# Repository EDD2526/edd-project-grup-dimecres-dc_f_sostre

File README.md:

# Projecte Eines Sostre Solar 

>**Autors: Nabel Khrourouch i Marc Baillo** 
>**Versió: 0.2 **

----------

## Objectiu

Dissenyar i implementar en una PCB, un sistema electronic del vehicle com es un sostre solar. S’implementara una etapa de regulacio, microcontrolador,  bus CAN, I2C / SPI, USART i botons. 
I que incloguiu les següents caracteristiques:
- Motor del vidre amb el seu final de carrera. 
- Motor de la cortineta.
- Llums ambientals (LED RGB amb bus digital)
- Mecanisme antiatrapament (sensor digital de corrent).

## Diagrama de blocs

### Descripció/funcionalitat de cada bloc

  * Power: En aquest bloc posem la partt relacionada con 2 etapes, la de la alimentació i la de potencia. (LDO y Buck converter i el H-Bridge)
  * Microcontrolador: en aquest bloc posem les parts que tenen molt que veure amb el microcontrolador com cristal oscilador, ICSP, botonera, filtre pi, reset manual, LEDs de prova.
  * Analógica: part del sistema que és analogic i per tant la agrupem, aquí veiem el sensor de anti-atrapament.
  * Digital: part on están els components més purament digitals, como el USART, el transceiver CAN, el Sensor de Final de Carrera o LED RGB. 

-----------

## Requisits / Especificacions

  * Alimentació; 12V, regulada a 3V3
  * Microcontrolador PIC24hj128gp502
  * Motor del vidre amb el seu final de carrera. 
  * Motor de la cortineta.
  * Llums ambientals (LED RGB amb bus digital)
  * Mecanisme antiatrapament (sensor digital de corrent).

-----------

## Components

| Descripció                        | Ref                        | Package                  | Datasheet | Proveïdor | Preu (per u) | Unitats |
|----------------------------------|----------------------------|--------------------------|-----------|-----------|--------------|---------|
| Microcontrolador                | PIC24HJ128GP502           | TQFP-44                  | [Datasheet](https://ww1.microchip.com/downloads/aemDocuments/documents/OTH/ProductDocuments/DataSheets/70293G.pdf) | [Mouser](https://www.mouser.es/ProductDetail/Microchip-Technology/PIC24HJ128GP504-E-PT?qs=Fllw7YelV3%252B64KTDe2rRTg%3D%3D) | 6,85€ | 1x |
| Regulador de Tensió             | LM1117                    | SOT-223 / TO-252-3       | [Datasheet](https://www.ti.com/lit/ds/symlink/lm1117.pdf) | [Mouser](https://www.mouser.es/ProductDetail/Texas-Instruments/LM1117IMPX-3.3-NOPB?qs=X1J7HmVL2ZG7K12CpArCeA%3D%3D) | 0,89€ | 1x |
| Buck Converter (DC/DC)          | LM2596                    | TO-220-5                 | [Datasheet](https://www.onsemi.com/pdf/datasheet/lm2596-d.pdf) | [Mouser](https://www.mouser.es/ProductDetail/onsemi/LM2596DSADJG?qs=atIEnC%2F2K4W1Dy%252BFjrRjIQ%3D%3D) | 2€ | 1x |
| H-Bridge (Doble)                | L298N                     | Multiwatt-15             | [Datasheet](https://www.st.com/resource/en/datasheet/l298.pdf) | [Mouser](https://www.mouser.es/ProductDetail/STMicroelectronics/L298N?qs=gr8Zi5OG3Mj6jDtNclcF9Q%3D%3D&srsltid=AfmBOoqfHqg2YnbNWZkkZ0kC8gS-It04lRCKKxTP2hRawLswU3FHokk-) | 9,94€ | 1x |
| Transceiver CAN                 | SN65HVD232DR                 | SOIC-8                   | [Datasheet](https://www.ti.com/lit/ds/symlink/sn65hvd230.pdf?ts=1777297017115&ref_url=https%253A%252F%252Fwww.ti.com%252Fproduct%252FSN65HVD230) | [Mouser](https://eu.mouser.com/ProductDetail/Texas-Instruments/SN65HVD232DR?qs=QViXGNcIEAtY%252BrViRMr46w%3D%3D) | 1,87€  | 1x |
| Driver USART                    | MAX3232                   | SSOP-16                  | [Datasheet](https://www.mouser.es/datasheet/3/1014/1/MAX3222-MAX3241.pdf) | [Mouser](https://www.mouser.es/ProductDetail/Analog-Devices-Maxim-Integrated/MAX3232CUE%2bT?qs=CDqwynd4ZNq6sBxRCl3%2FVw%3D%3D) | 6,99€ | 1x |
| Conector                        | DE9                       | DSUB-9_Socket            | [Datasheet](https://www.te.com/commerce/DocumentDelivery/DDEController?Action=srchrtrv&DocNm=2301843&DocType=Customer+Drawing&DocLang=English&PartCntxt=2301843-1&DocFormat=pdf) | [Mouser](https://www.mouser.es/ProductDetail/TE-Connectivity-AMP/2301843-1?qs=rrS6PyfT74crws9wAQVNoA%3D%3D&mgh=1&vip=1&utm_id=19103542967&utm_source=google&utm_medium=cpc&utm_marketing_tactic=emeacorp&gad_source=1&gad_campaignid=19103548274&gbraid=0AAAAADn_wf2KTMAEN9aavrmuZXjiN2vqm&gclid=Cj0KCQjw7IjOBhDyARIsAFzrWQzWx8kAOC9-xeCib2TtXzouOFVkeyjK2X-mWbgX7vQpQhIDmcFKVOEaAr35EALw_wcB) | 1,9€ | 2x |
| Conector (Batería i Motors)                       | 282837-2                       | THT          | [Datasheet](https://www.te.com/commerce/DocumentDelivery/DDEController?Action=srchrtrv&DocNm=1-1773458-1_EURO_STYLE_QRG&DocType=Data%20Sheet&DocLang=English&PartCntxt=3-282837-2&DocFormat=pdf) | [Mouser](https://www.mouser.es/ProductDetail/TE-Connectivity/3-282837-2?qs=gdajpSf3VLdF%252BeXqJMAnlA%3D%3D&utm_id=20109199436&utm_source=google&utm_medium=cpc&utm_marketing_tactic=emeacorp&gad_source=1&gad_campaignid=20109199436&gbraid=0AAAAADn_wf3bSykfoqBB3E0CfDtWEe629&gclid=Cj0KCQjw7IjOBhDyARIsAFzrWQyU83zMWuFV4gqDL4u1LgEcrHvitAufowkzTkPBhEg_k3zvYB4tBVIaAj3AEALw_wcB) | 9,38€ | 3x |
| Sensor (corrent) Anti-Atrapament              | INA219                    | SOIC-8                      | [Datasheet](https://www.ti.com/lit/ds/symlink/ina219.pdf) | [Mouser](https://www.mouser.es/ProductDetail/) | 4,23€ | 2x |
| Sensor Final de Carrera         | A1101                     | SOT-23                   | [Datasheet](https://www.allegromicro.com/~/media/files/datasheets/a110x-datasheet.pdf) | [Mouser](https://www.mouser.es/ProductDetail/Allegro-MicroSystems/A1101EUA-T?qs=pUKx8fyJudAoca%252BrN0Sfug%3D%3D&srsltid=AfmBOopmzx3dJfmaMgARzIOmuFdzof038kPjXIFZjNx3_Dk0axwEeuXz) | 1,18€ | 2x |
| Opamp Doble Comparador        | LM393                     | SOIC-8                  | [Datasheet](https://www.ti.com/lit/ds/symlink/lm2903b.pdf?ts=1774335179874&ref_url=https%253A%252F%252Fwww.mouser.pl%252F) | [Mouser](https://www.mouser.es/ProductDetail/Texas-Instruments/LM393AP?qs=LfG3tU9ud8C8WR6rae7e8w%3D%3D&utm_id=20109199436&utm_source=google&utm_medium=cpc&utm_marketing_tactic=emeacorp&gad_source=1&gad_campaignid=20109199436&gbraid=0AAAAADn_wf3bSykfoqBB3E0CfDtWEe629&gclid=Cj0KCQjw7IjOBhDyARIsAFzrWQwk6DXPkYJ3-Ag5UdBtY40izdCAfFJImBQIx_JyaWhi5W70RpnD0e8aAgx9EALw_wcB) | 0,31 | 1x |
| Cristal Oscilador               | ECS-80-20-20BM-EN-TR      | 7mm x 5mm                | [Datasheet](https://www.mouser.es/datasheet/3/294/1/csm_8mr.pdf) | [Mouser](https://www.mouser.es/ProductDetail/ECS/ECS-80-20-20BM-EN-TR?qs=3Rah4i%252BhyCEvSjMjFbrNOA%3D%3D&utm_id=9882080341&utm_source=google&utm_medium=cpc&utm_marketing_tactic=emeacorp&gad_source=1&gad_campaignid=9882080341&gbraid=0AAAAADn_wf2VPwruzVVuU5TdtfDNM-71c&gclid=CjwKCAjwpcTNBhA5EiwAdO1S9kbEmbKF8UUMwaVP0zWJXkCwjEh6ns86OOaH_PQxj7KPIVRFoQ-tjhoCMYIQAvD_BwE) | 0,86€ | 1x |
| Ferrita                         | BLM21                     | 0805                     | [Datasheet](https://www.mouser.es/datasheet/3/76/1/ENFA0005.pdf) | [Mouser](https://www.mouser.es/ProductDetail/Murata-Electronics/BLM21PG600SN1D?qs=LbqjZSvnDswFXSg06XQ50A%3D%3D&utm_id=9882080341&utm_source=google&utm_medium=cpc&utm_marketing_tactic=emeacorp&gad_source=1&gad_campaignid=9882080341&gbraid=0AAAAADn_wf2r1gIBG4HB31JwCLchDktw_&gclid=Cj0KCQjw9-PNBhDfARIsABHN6-1kCnzr_LU1mZd8ISSiD6a4Y2yPfWM2slAP8zejLYN4QiWVlEgd_j4aAjKhEALw_wcB) | 0,10€ | 1x |
| Switch (Pulsador) Reset y Botonera                 | B3F-1002                  | THT                      | [Datasheet](https://www.mouser.es/datasheet/3/39/1/en_b3f.pdf) | [Mouser](https://www.mouser.es/ProductDetail/Omron-Electronics/B3F-1002?qs=lK7M36XCk6Jk6Tf1a0ilbA%3D%3D&mgh=1&vip=1&utm_source=chatgpt.com) | 0,27€ | 6x |
| LED blau                        | LTST-C170TBKT             | LED_SMD                     | [Datasheet](https://www.mouser.com/catalog/specsheets/Lite-On-LTST-C170TBKT.pdf) | [Mouser](https://www.mouser.es/ProductDetail/LITEON/LTST-C170TBKT?qs=0uL0gcxEMop2ooGmIUzw3A%3D%3D&mgh=1&vip=1&utm_source=chatgpt.com) | 0,23€ | 1x |
| LED vermell                     | LTST-C170KRKT             | LED_SMD                     | [Datasheet](https://www.mouser.com/catalog/specsheets/Lite-On-LTST-C170KRKT.pdf) | [Mouser](https://www.mouser.es/ProductDetail/LITEON/LTST-C170KRKT?qs=NUb82WqeCyrVOID%2Fxt4rgA%3D%3D&utm_id=9882080341&utm_source=google&utm_medium=cpc&utm_marketing_tactic=emeacorp&gad_source=1&gad_campaignid=9882080341&gbraid=0AAAAADn_wf35b0MW3nfCvSzMlg6XwcaGU&gclid=CjwKCAjwyYPOBhBxEiwAgpT8P6xYGFYLA1kJHVwio65sFBFYBpuG5qPQD4Bkm8pgxI7bRmXtEGCxWBoC7pMQAvD_BwE) | 0,14€ | 1x |
| LED RGB                         | WS2812                    | LED_SMD                 | [Datasheet](https://www.tme.eu/Document/01c0100fee68667af99767edc3a7fee2/WS2812B-MINI.pdf) | [TME](https://www.tme.eu/es/details/ws2812b-mini/leds-smd-de-colores/worldsemi/?utm_source=google&utm_medium=cpc&utm_campaign=HISZPANIA%20%5BDSA%5D&utm_content=&campaign_id=18880888776&gad_source=1&gad_campaignid=18880888776&gbraid=0AAAAADyylhLJURluAY7jUeNc8-F-2bfAx&gclid=Cj0KCQjw7IjOBhDyARIsAFzrWQzO_PW3O0VVMhyARWr_1LRVY-vRQsT44Hck0vcMLTjOFT9BO_EXdCEaAkMFEALw_wcB) | 0,42€ | 1x |
| Level shifter (buffer)                        | 74AHCT1G125            | SOT-553              | [Datasheet](https://www.ti.com/lit/ds/symlink/sn74ahct1g125.pdf?ts=1774340206599&ref_url=https%253A%252F%252Fwww.mouser.dk%252F) | [Mouser](https://www.mouser.es/ProductDetail/Texas-Instruments/74AHCT1G125DBVTG4?qs=AsTZqt%2FmeqnddshDG5FV%2Fw%3D%3D&utm_id=20109199436&utm_source=google&utm_medium=cpc&utm_marketing_tactic=emeacorp&gad_source=1&gad_campaignid=20109199436&gbraid=0AAAAADn_wf3bSykfoqBB3E0CfDtWEe629&gclid=Cj0KCQjw7IjOBhDyARIsAFzrWQxSsxXdPjF95Q5vX5TJ7WjE_NFE_Jxv0JufhHPBQC8U8gs4R3YIGEkaAvcBEALw_wcB) | 0,93€ | 1x |

-----------

## Historial de canvis

| Data     | Autor           | Branch | Versió   | Descripció                                                                 |
|----------|-----------------|--------|----------|----------------------------------------------------------------------------|
| 10/03/26 | Nabel i Marc    | Master | versió 1 | Seleccionem els components i creem la primera versió del Diagrama de Bloc |
| 14/03/26 | Nabel           | Master | versió 2 | Actualització del Diagrama de Bloc                                        |
| 16/03/26 | Marc            | Master | versió 1 | Esquemàtic: creació dels subapartats del projecte                         |
| 17/03/26 | Marc            | Master | versió 2 | Esquemàtic: faig la part del uC i de Digital                              |
| 17/03/26 | Nabel           | Master | versió 3 | Esquemàtic: faig la part de power i analògica                             |
| 22/03/26 | Marc            | Master | versió 4 | Esquemàtic: correcció d’errades i assignació de footprints                |
| 24/03/26 | Nabel           | Master | versió 1 | Layout: faig el rutejat de la majoria dels components                     |
| 24/03/26 | Marc            | Master | versió 2 | Layout: corregeixo algunes coses                                          |
| 30/03/26 | Nabel           | Master | versió 3 | Layout: rutejat part Digital                                              |
| 31/03/26 | Marc            | Master | versió 4 | Layout: treballo part potencia, H_Bridge                                  |
| 08/04/26 | Marc i Nabel    | Master | versió 5 | Layout: treballem a classe i l'intentem posar a punt                      |
| 15/04/26 | Marc i Nabel    | Master | versió 6 | Layout: corregim algunes coses com tema de plans i posar plans de massa digital i power |
| 27/04/26 | Nabel           | Master | versió 1 | Faig el pressupost                                                       |
| 28/04/26 | Marc            | Master | versió 7 | Layout: acabo el Layout posant uns canvis proposats pel professor         |

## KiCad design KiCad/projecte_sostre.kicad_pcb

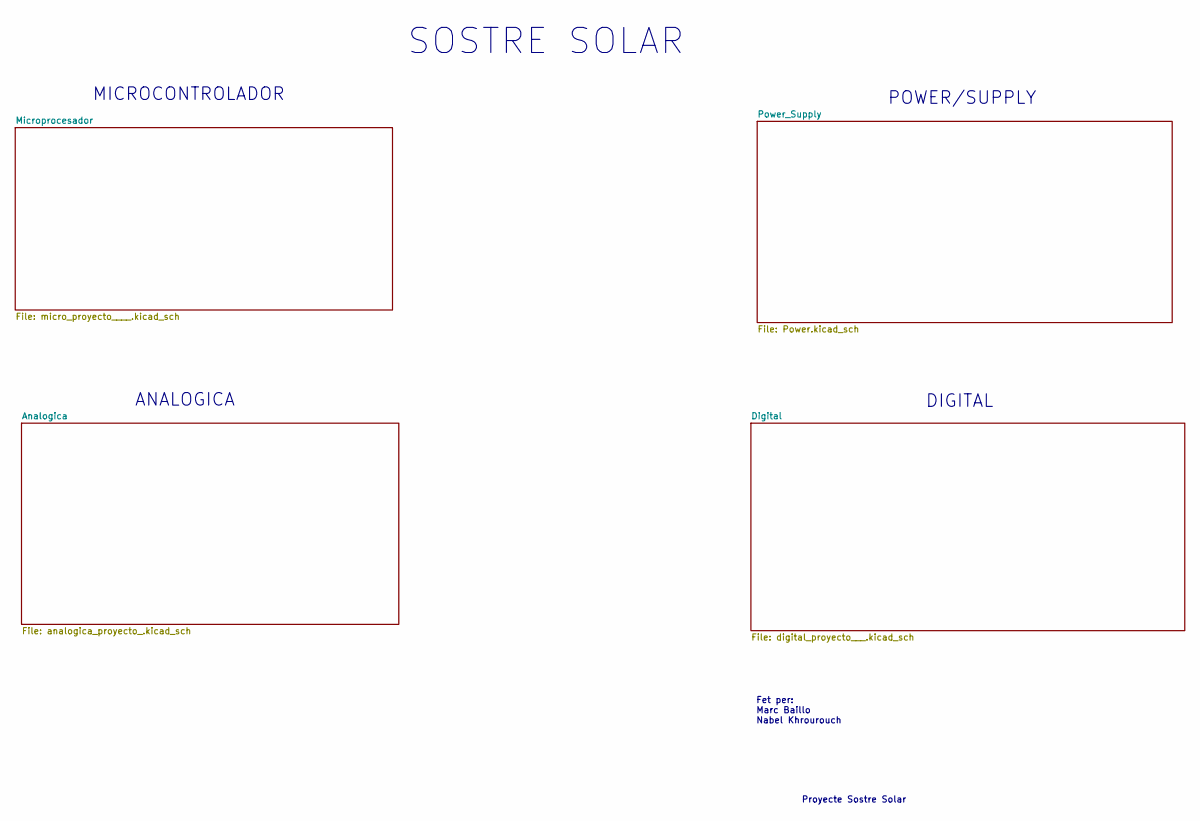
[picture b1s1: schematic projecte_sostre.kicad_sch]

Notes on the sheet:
SOSTRE SOLAR
Proyecte Sostre Solar
MICROCONTROLADOR
POWER/SUPPLY
ANALOGICA
Fet per: Marc Baillo Nabel Khrourouch
DIGITAL

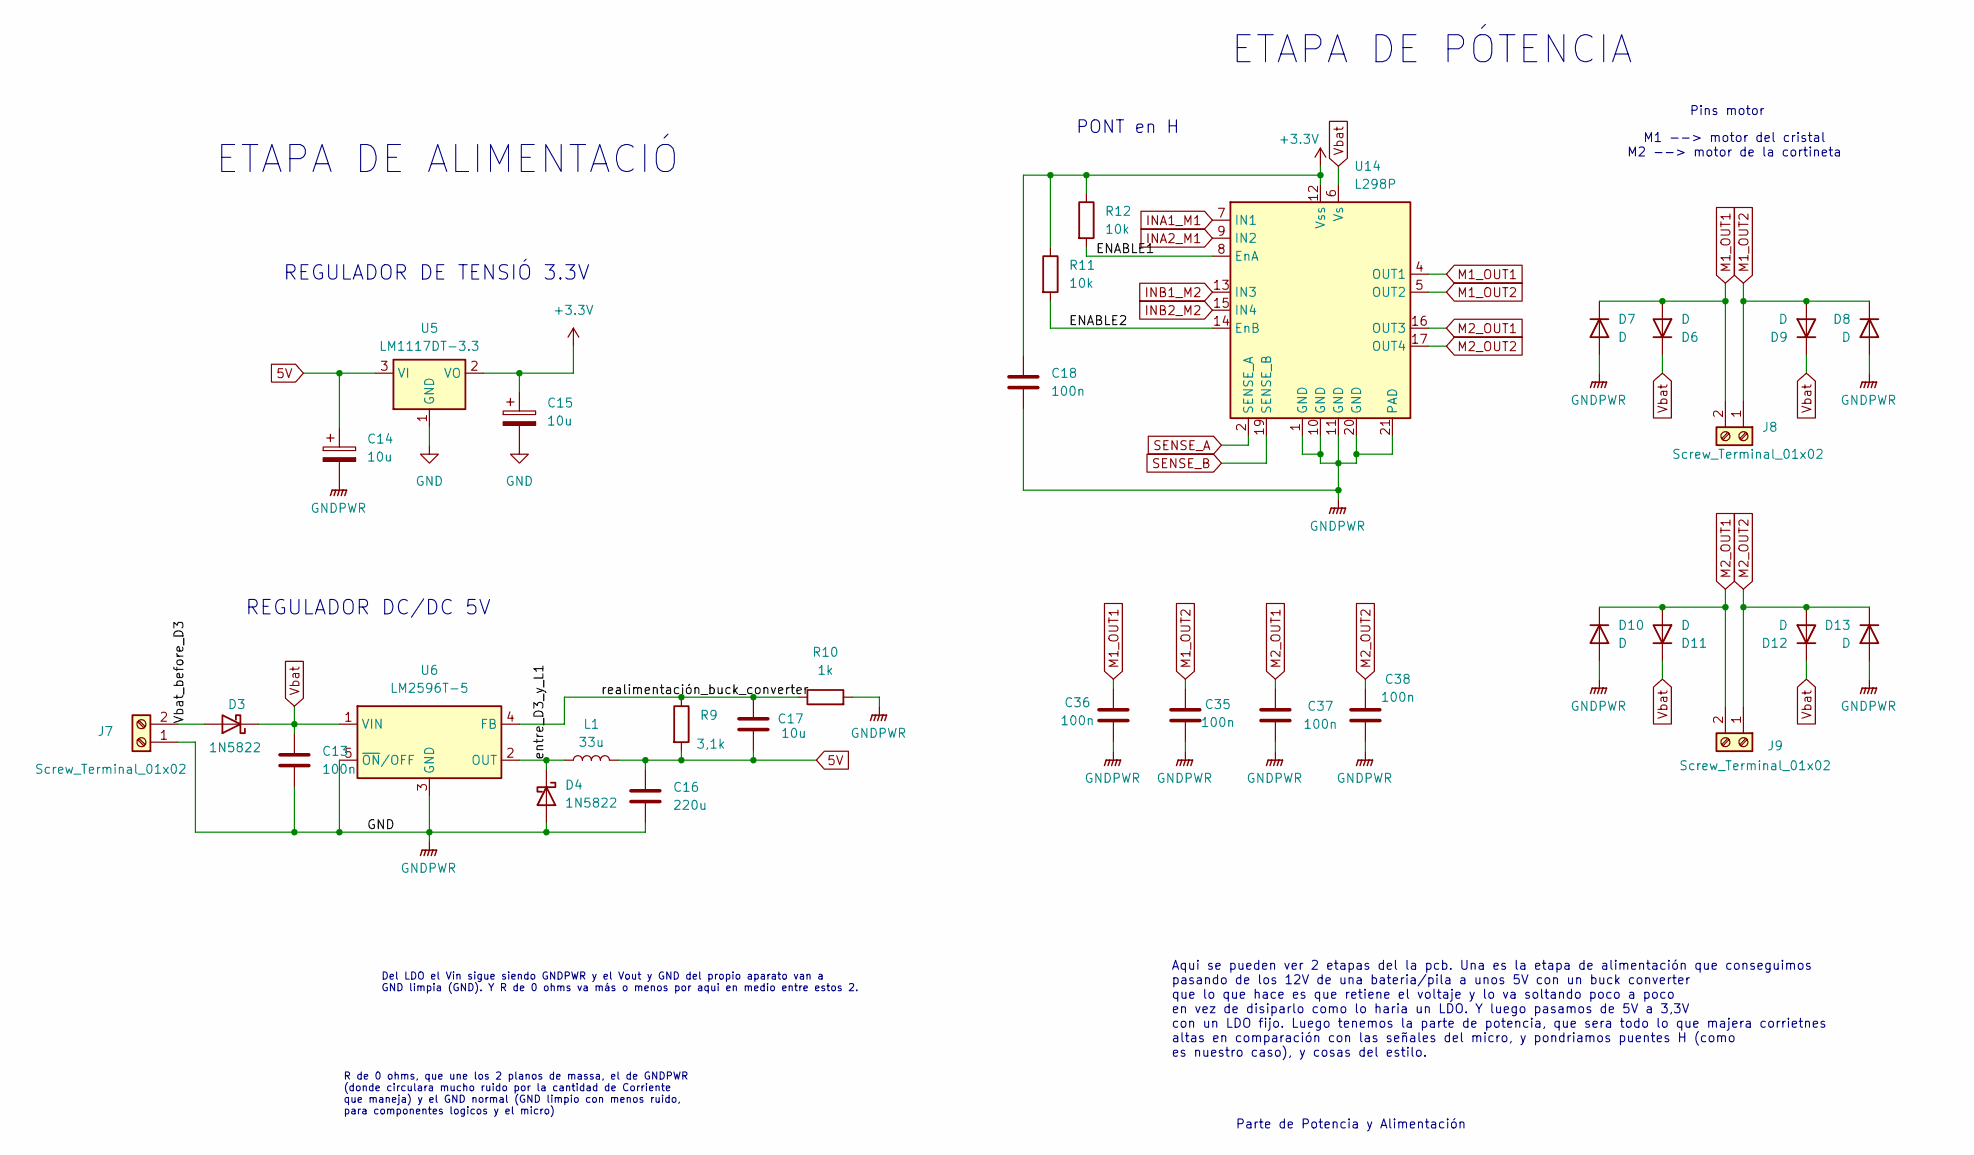
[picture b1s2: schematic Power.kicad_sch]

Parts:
C13, C18, C35, C36, C37, C38: 100n; C_0805_2012Metric
C14, C15, C17: 10u; C_0805_2012Metric
C16: 220u; C_0805_2012Metric
D3, D4: 1N5822; D_DO-201AD_P15.24mm_Horizontal
D6, D7, D8, D9, D10, D11, D12, D13: D; D_SMA
J7, J8, J9: Screw_Terminal_01x02; TerminalBlock_MaiXu_MX126-5.0-02P_1x02_P5.00mm
L1: 33u; L_1210_3225Metric
R9: 3,1k; R_0805_2012Metric
R10: 1k; R_0805_2012Metric
R11, R12: 10k; R_0805_2012Metric
U5: LM1117DT-3.3; TO-252-3_TabPin2
U6: LM2596T-5; TO-220-5_P3.4x3.7mm_StaggerOdd_Lead3.8mm_Vertical
U14: L298P; Infineon_SOIC-20W_7.6x12.8mm_P1.27mm

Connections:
5V: C14.1, C16.1, C17.2, L1.2, R9.2, U5.3 (VI); also elsewhere on the board
+3.3V: C15.1, C18.1, R11.1, R12.1, U5.2 (VO), U14.12 (Vss); also elsewhere on the board
/Power_Supply/ENABLE1: R12.2, U14.8 (EnA)
/Power_Supply/ENABLE2: R11.2, U14.14 (EnB)
/Power_Supply/Vbat_before_D3: D3.2 (A), J7.2
/Power_Supply/entre_D3_y_L1: D4.1 (K), L1.1, U6.2 (OUT)
/Power_Supply/realimentación_buck_converter: C17.1, R9.1, R10.1, U6.4 (FB)
GND: C13.2, C14.2, C15.2, C16.2, C18.2, C35.2, C36.2, C37.2, C38.2, D4.2 (A), D7.2 (A), D8.2 (A), D10.2 (A), D13.2 (A), J7.1, R10.2, U5.1 (GND), U6.3 (GND), U6.5 (~ON/OFF), U14.1 (GND), U14.10 (GND), U14.11 (GND), U14.20 (GND), U14.21 (PAD); also elsewhere on the board
INA1_M1: U14.7 (IN1); also elsewhere on the board
INA2_M1: U14.9 (IN2); also elsewhere on the board
INB1_M2: U14.13 (IN3); also elsewhere on the board
INB2_M2: U14.15 (IN4); also elsewhere on the board
M1_OUT1: C36.1, D6.2 (A), D7.1 (K), J8.2, U14.4 (OUT1)
M1_OUT2: C35.1, D8.1 (K), D9.2 (A), J8.1, U14.5 (OUT2)
M2_OUT1: C37.1, D10.1 (K), D11.2 (A), J9.2, U14.16 (OUT3)
M2_OUT2: C38.1, D12.2 (A), D13.1 (K), J9.1, U14.17 (OUT4)
SENSE_A: U14.2 (SENSE_A); also elsewhere on the board
SENSE_B: U14.19 (SENSE_B); also elsewhere on the board
Vbat: C13.1, D3.1 (K), D6.1 (K), D9.1 (K), D11.1 (K), D12.1 (K), U6.1 (VIN), U14.6 (Vs); also elsewhere on the board

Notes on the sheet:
Parte de Potencia y Alimentación
PONT en H
R de 0 ohms, que une los 2 planos de massa, el de GNDPWR (donde circulara mucho ruido por la cantidad de Corriente que maneja) y el GND normal (GND limpio con menos ruido, para componentes logicos y el micro)
Aqui se pueden ver 2 etapas del la pcb. Una es la etapa de alimentación que conseguimos pasando de los 12V de una bateria/pila a unos 5V con un buck converter que lo que hace es que retiene el voltaje y lo va soltando poco a poco en vez de disiparlo como lo haria un LDO. Y luego pasamos de 5V a 3,3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
M1 --> motor del cristal M2 --> motor de la cortineta
REGULADOR DC/DC 5V
ETAPA DE PÓTENCIA
ETAPA DE ALIMENTACIÓ
REGULADOR DE TENSIÓ 3.3V
Del LDO el Vin sigue siendo GNDPWR y el Vout y GND del propio aparato van a GND limpia (GND). Y R de 0 ohms va más o menos por aqui en medio entre estos 2.
Pins motor

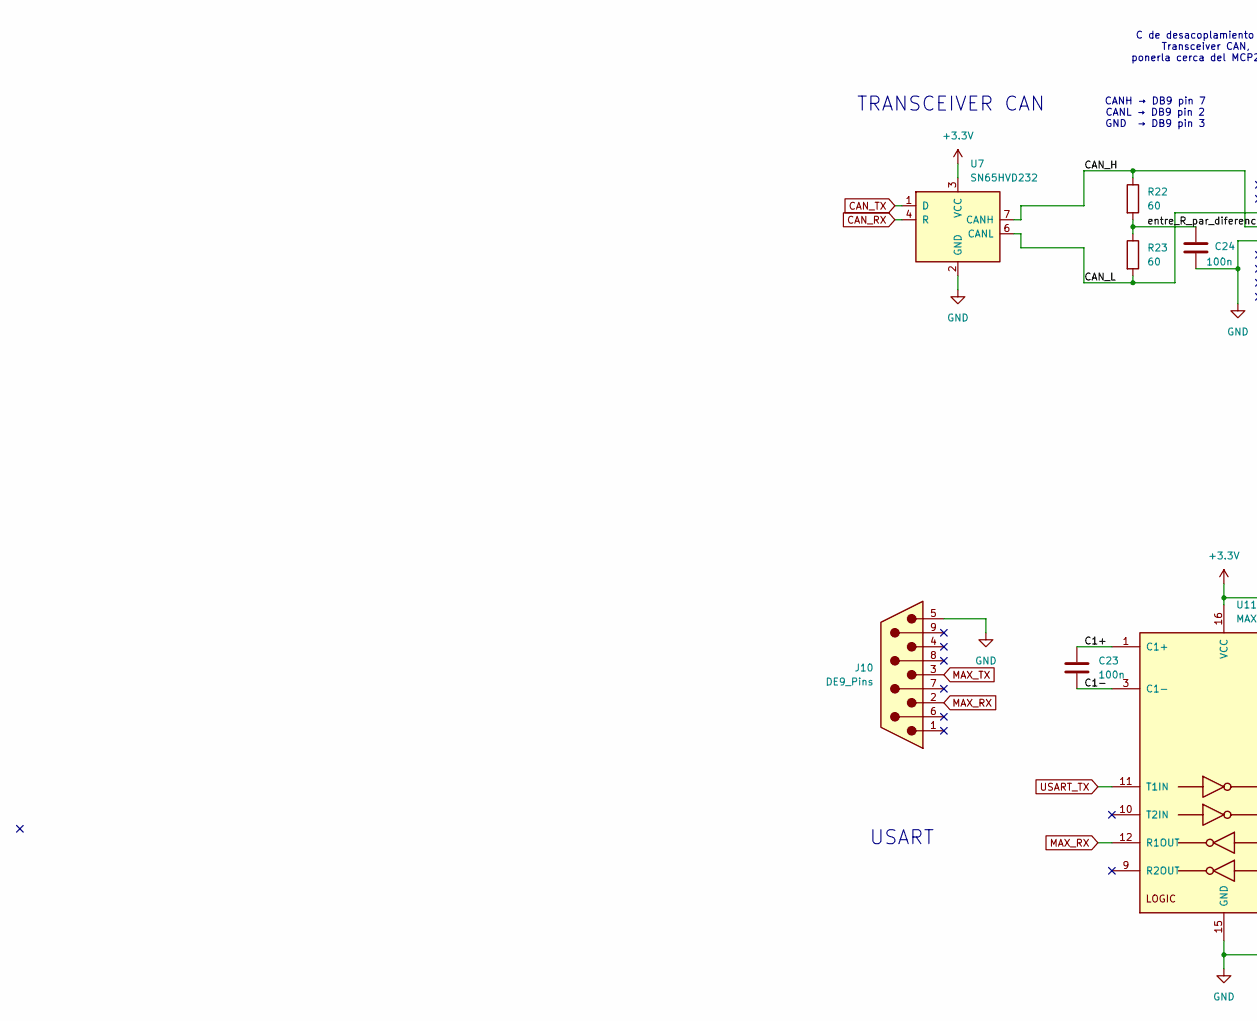
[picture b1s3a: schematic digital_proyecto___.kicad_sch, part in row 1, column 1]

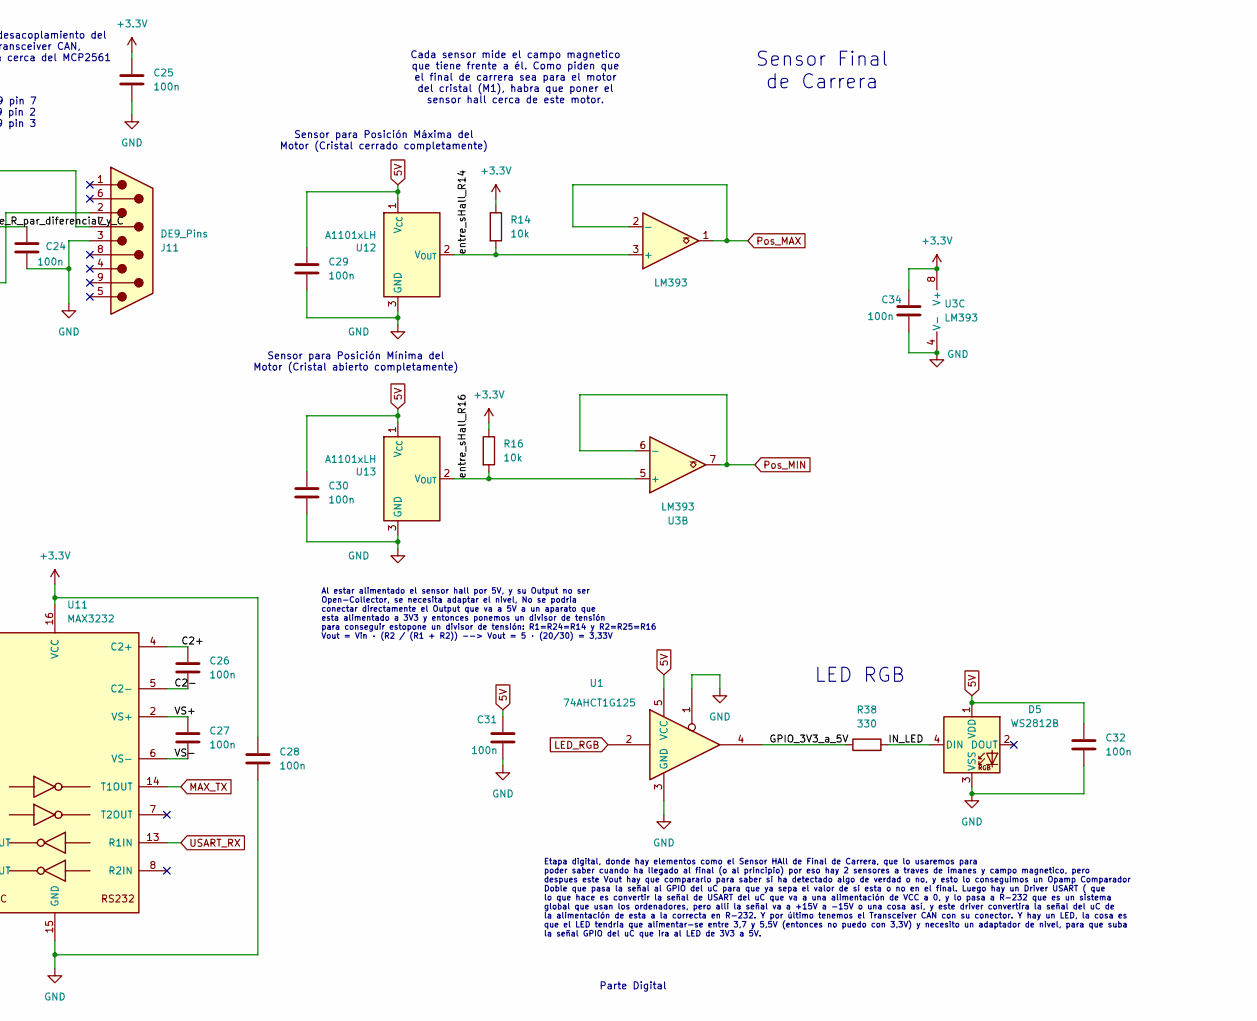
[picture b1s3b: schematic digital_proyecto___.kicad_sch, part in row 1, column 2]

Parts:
C23, C24, C25, C26, C27, C28, C29, C30, C31, C32, C34: 100n; C_0805_2012Metric
D5: WS2812B; LED_WS2812B_PLCC4_5.0x5.0mm_P3.2mm
J10, J11: DE9_Pins; DSUB-9_Pins_Horizontal_P2.77x2.54mm_EdgePinOffset9.40mm
R14, R16: 10k; R_0805_2012Metric
R22, R23: 60; R_0805_2012Metric
R38: 330; R_0805_2012Metric
U1: 74AHCT1G125; SOT-23-5_HandSoldering
U3: LM393; SOIC-8_3.9x4.9mm_P1.27mm
U7: SN65HVD232; SOIC-8_3.9x4.9mm_P1.27mm
U11: MAX3232; SOIC-16_3.9x9.9mm_P1.27mm
U12, U13: A1101xLH; SOT-23W

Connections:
5V: C29.1, C30.1, C31.1, C32.1, D5.1 (VDD), U1.5 (VCC), U12.1 (V_{CC}), U13.1 (V_{CC}); also elsewhere on the board
+3.3V: C25.1, C28.1, C34.1, R14.1, R16.1, U3.8 (V+), U7.3 (VCC), U11.16 (VCC); also elsewhere on the board
/Digital/C1+: C23.1, U11.1 (C1+)
/Digital/C1-: C23.2, U11.3 (C1-)
/Digital/C2+: C26.1, U11.4 (C2+)
/Digital/C2-: C26.2, U11.5 (C2-)
/Digital/CAN_H: J11.7, R22.1, U7.7 (CANH)
/Digital/CAN_L: J11.2, R23.2, U7.6 (CANL)
/Digital/GPIO_3V3_a_5V: R38.1, U1.4
/Digital/IN_LED: D5.4 (DIN), R38.2
/Digital/VS+: C27.1, U11.2 (VS+)
/Digital/VS-: C27.2, U11.6 (VS-)
/Digital/entre_R_par_diferencial_y_C: C24.1, R22.2, R23.1
/Digital/entre_sHall_R14: R14.2, U3.3 (+), U12.2 (V_{OUT})
/Digital/entre_sHall_R16: R16.2, U3.5 (+), U13.2 (V_{OUT})
CAN_RX: U7.4 (R); also elsewhere on the board
CAN_TX: U7.1 (D); also elsewhere on the board
GND: C24.2, C25.2, C28.2, C29.2, C30.2, C31.2, C32.2, C34.2, D5.3 (VSS), J10.5, J11.3, U1.1, U1.3 (GND), U3.4 (V-), U7.2 (GND), U11.15 (GND), U12.3 (GND), U13.3 (GND); also elsewhere on the board
LED_RGB: U1.2; also elsewhere on the board
MAX_RX: J10.2, U11.12 (R1OUT)
MAX_TX: J10.3, U11.14 (T1OUT)
Pos_MAX: U3.1, U3.2 (-); also elsewhere on the board
Pos_MIN: U3.6 (-), U3.7; also elsewhere on the board
USART_RX: U11.13 (R1IN); also elsewhere on the board
USART_TX: U11.11 (T1IN); also elsewhere on the board

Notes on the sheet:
USART
Etapa digital, donde hay elementos como el Sensor HAll de Final de Carrera, que lo usaremos para poder saber cuando ha llegado al final (o al principio) por eso hay 2 sensores a traves de imanes y campo magnetico, pero despues este Vout hay que compararlo para saber si ha detectado algo de verdad o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
Parte Digital
Al estar alimentado el sensor hall por 5V, y su Output no ser Open-Collector, se necesita adaptar el nivel, No se podria conectar directamente el Output que va a 5V a un aparato que esta alimentado a 3V3 y entonces ponemos un divisor de tensión para conseguir estopone un divisor de tensión: R1=R24=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
TRANSCEIVER CAN
Sensor para Posición Mínima del Motor (Cristal abierto completamente)
CANH → DB9 pin 7 CANL → DB9 pin 2 GND → DB9 pin 3
Cada sensor mide el campo magnetico que tiene frente a él. Como piden que el final de carrera sea para el motor del cristal (M1), habra que poner el sensor hall cerca de este motor.
C de desacoplamiento del Transceiver CAN, ponerla cerca del MCP2561
Sensor para Posición Máxima del Motor (Cristal cerrado completamente)
Sensor Final de Carrera
LED RGB

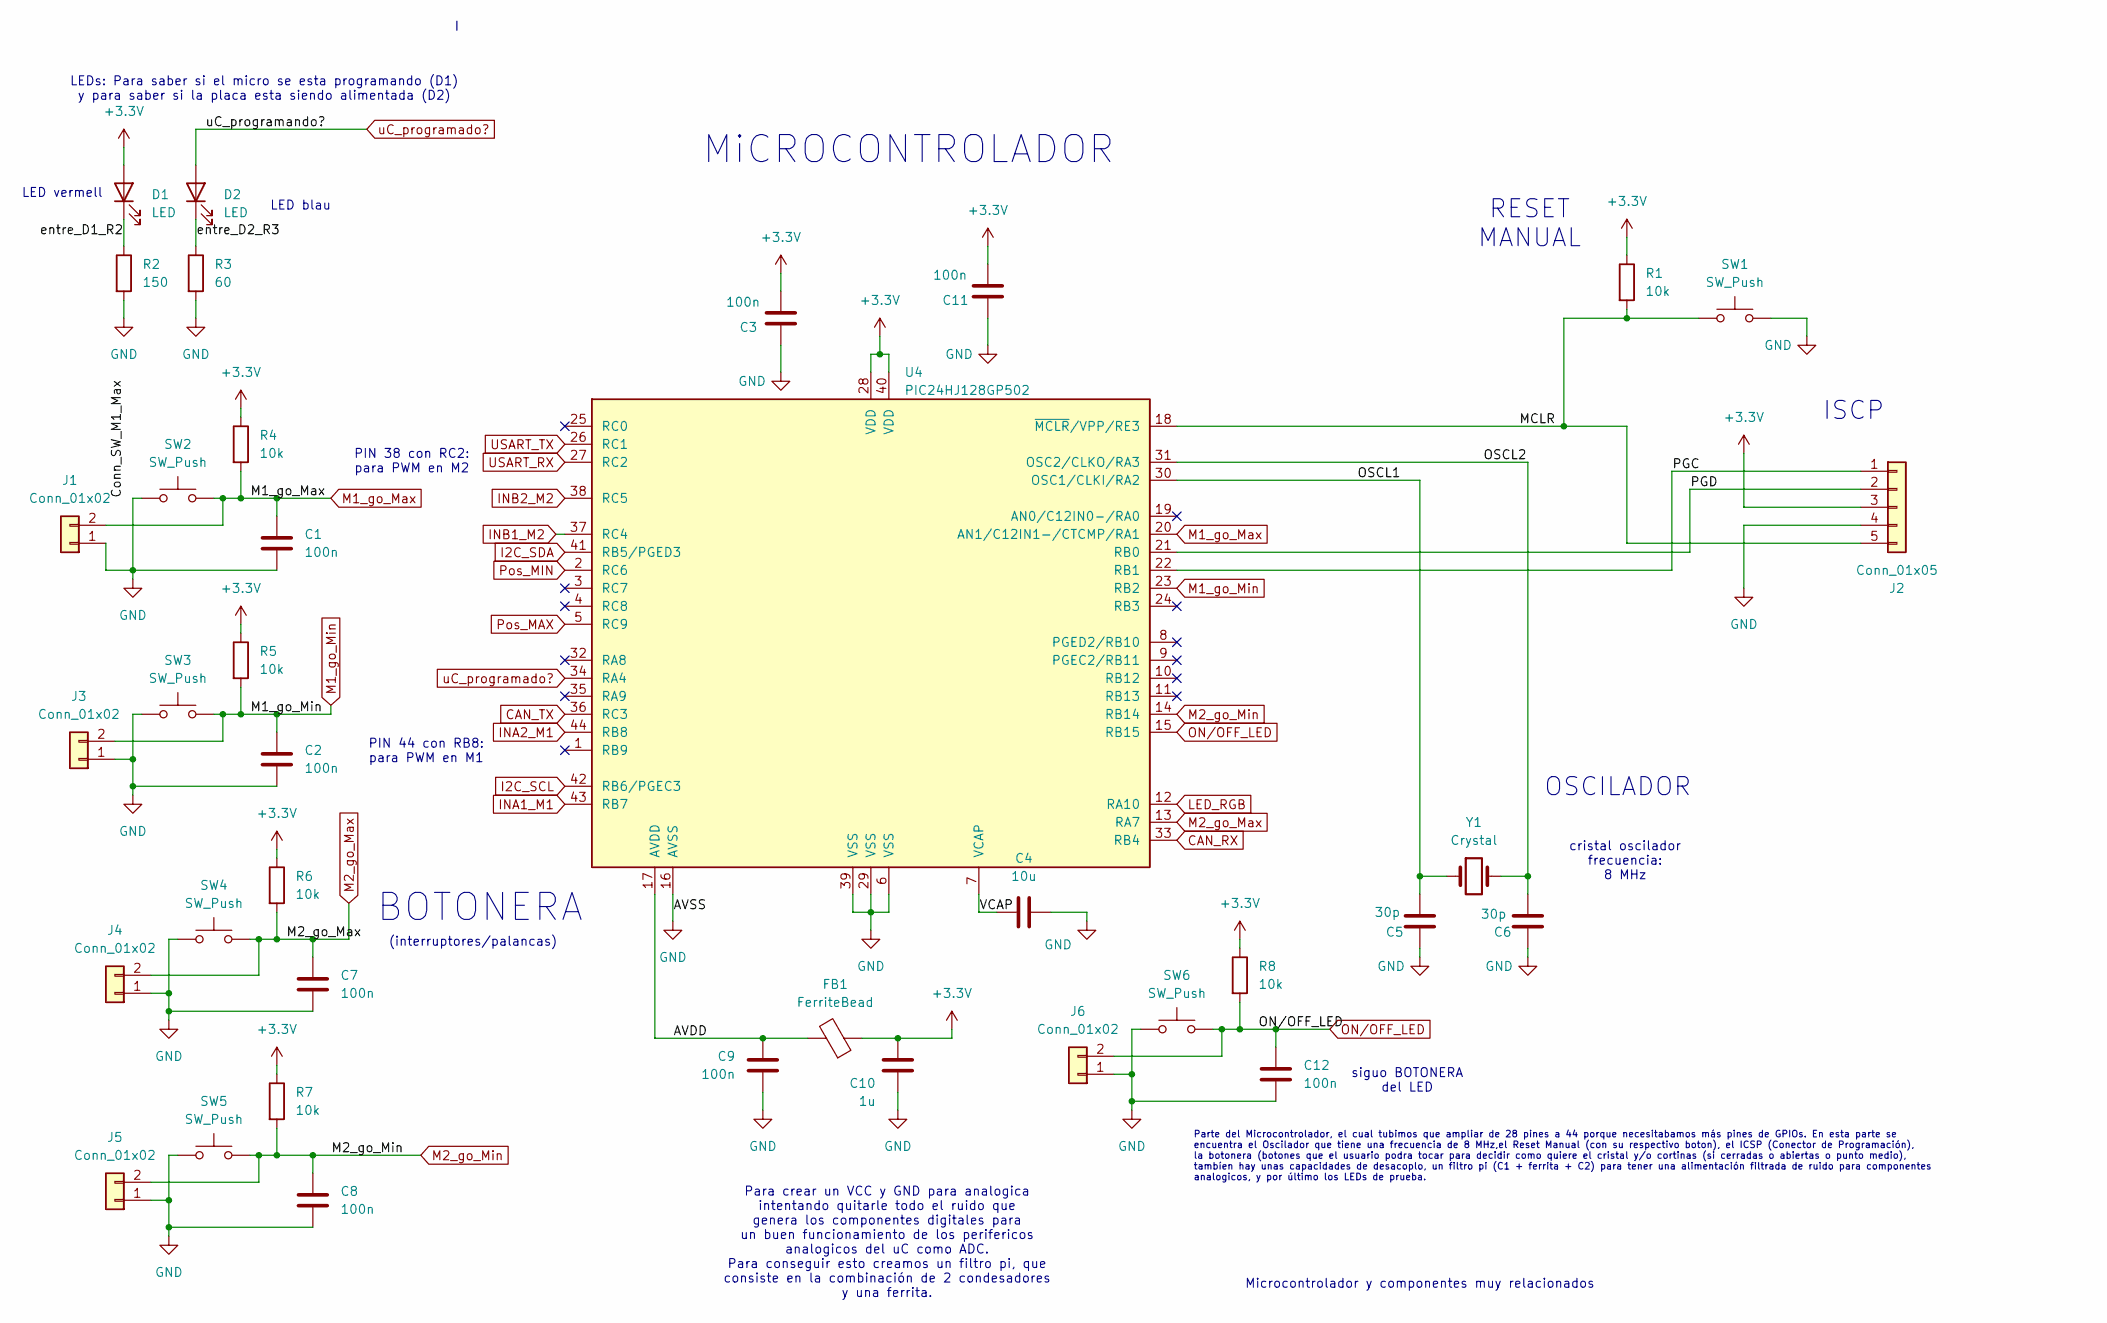
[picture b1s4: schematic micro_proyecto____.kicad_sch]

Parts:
C1, C2, C3, C7, C8, C9, C11, C12: 100n; C_0805_2012Metric
C4: 10u; C_0805_2012Metric
C5, C6: 30p; C_0805_2012Metric
C10: 1u; C_0805_2012Metric
D1, D2: LED; LED_0805_2012Metric
FB1: FerriteBead; R_0805_2012Metric
J1, J3, J4, J5, J6: Conn_01x02; PinHeader_1x02_P2.54mm_Vertical
J2: Conn_01x05; PinHeader_1x05_P2.54mm_Vertical
R1, R4, R5, R6, R7, R8: 10k; R_0805_2012Metric
R2: 150; R_0805_2012Metric
R3: 60; R_0805_2012Metric
SW1, SW2, SW3, SW4, SW5, SW6: SW_Push; SW_PUSH_6mm
U4: PIC24HJ128GP502; TQFP-44_10x10mm_P0.8mm
Y1: Crystal; Crystal_HC52-6mm_Vertical

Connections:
+3.3V: C3.2, C10.1, C11.2, D1.2 (A), FB1.1, J2.3, R1.1, R4.1, R5.1, R6.1, R7.1, R8.1, U4.28 (VDD), U4.40 (VDD); also elsewhere on the board
/Microprocesador/AVDD: C9.1, FB1.2, U4.17 (AVDD)
/Microprocesador/MCLR: J2.5, R1.2, SW1.1, U4.18 (~MCLR/VPP/RE3)
/Microprocesador/OSCL1: C5.2, U4.30 (OSC1/CLKI/RA2), Y1.1
/Microprocesador/OSCL2: C6.2, U4.31 (OSC2/CLKO/RA3), Y1.2
/Microprocesador/PGC: J2.1, U4.22 (RB1)
/Microprocesador/PGD: J2.2, U4.21 (RB0)
/Microprocesador/VCAP: C4.2, U4.7 (VCAP)
/Microprocesador/entre_D1_R2: D1.1 (K), R2.1
/Microprocesador/entre_D2_R3: D2.1 (K), R3.1
CAN_RX: U4.33 (RB4); also elsewhere on the board
CAN_TX: U4.36 (RC3); also elsewhere on the board
GND: C1.2, C2.2, C3.1, C4.1, C5.1, C6.1, C7.2, C8.2, C9.2, C10.2, C11.1, C12.2, J1.1, J2.4, J3.1, J4.1, J5.1, J6.1, R2.2, R3.2, SW1.2, SW2.1, SW3.1, SW4.1, SW5.1, SW6.1, U4.6 (VSS), U4.16 (AVSS), U4.29 (VSS), U4.39 (VSS); also elsewhere on the board
I2C_SCL: U4.42 (RB6/PGEC3); also elsewhere on the board
I2C_SDA: U4.41 (RB5/PGED3); also elsewhere on the board
INA1_M1: U4.43 (RB7); also elsewhere on the board
INA2_M1: U4.44 (RB8); also elsewhere on the board
INB1_M2: U4.37 (RC4); also elsewhere on the board
INB2_M2: U4.38 (RC5); also elsewhere on the board
LED_RGB: U4.12 (RA10); also elsewhere on the board
M1_go_Max: C1.1, J1.2, R4.2, SW2.2, U4.20 (AN1/C12IN1-/CTCMP/RA1)
M1_go_Min: C2.1, J3.2, R5.2, SW3.2, U4.23 (RB2)
M2_go_Max: C7.1, J4.2, R6.2, SW4.2, U4.13 (RA7)
M2_go_Min: C8.1, J5.2, R7.2, SW5.2, U4.14 (RB14)
ON/OFF_LED: C12.1, J6.2, R8.2, SW6.2, U4.15 (RB15)
Pos_MAX: U4.5 (RC9); also elsewhere on the board
Pos_MIN: U4.2 (RC6); also elsewhere on the board
USART_RX: U4.27 (RC2); also elsewhere on the board
USART_TX: U4.26 (RC1); also elsewhere on the board
uC_programado?: D2.2 (A), U4.34 (RA4)

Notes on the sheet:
MiCROCONTROLADOR
LEDs: Para saber si el micro se esta programando (D1) y para saber si la placa esta siendo alimentada (D2)
LED vermell
Parte del Microcontrolador, el cual tubimos que ampliar de 28 pines a 44 porque necesitabamos más pines de GPIOs. En esta parte se encuentra el Oscilador que tiene una frecuencia de 8 MHz,el Reset Manual (con su respectivo boton), el ICSP (Conector de Programación), la botonera (botones que el usua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
RESET MANUAL
cristal oscilador frecuencia: 8 MHz
ISCP
Para crear un VCC y GND para analogica intentando quitarle todo el ruido que genera los componentes digitales para un buen funcionamiento de los perifericos analogicos del uC como ADC. Para conseguir esto creamos un filtro pi, que consiste en la combinación de 2 condesadores y una ferrita.
Microcontrolador y componentes muy relacionados
OSCILADOR
LED blau
BOTONERA
PIN 38 con RC2: para PWM en M2
PIN 44 con RB8: para PWM en M1
(interruptores/palancas)
siguo BOTONERA del LED

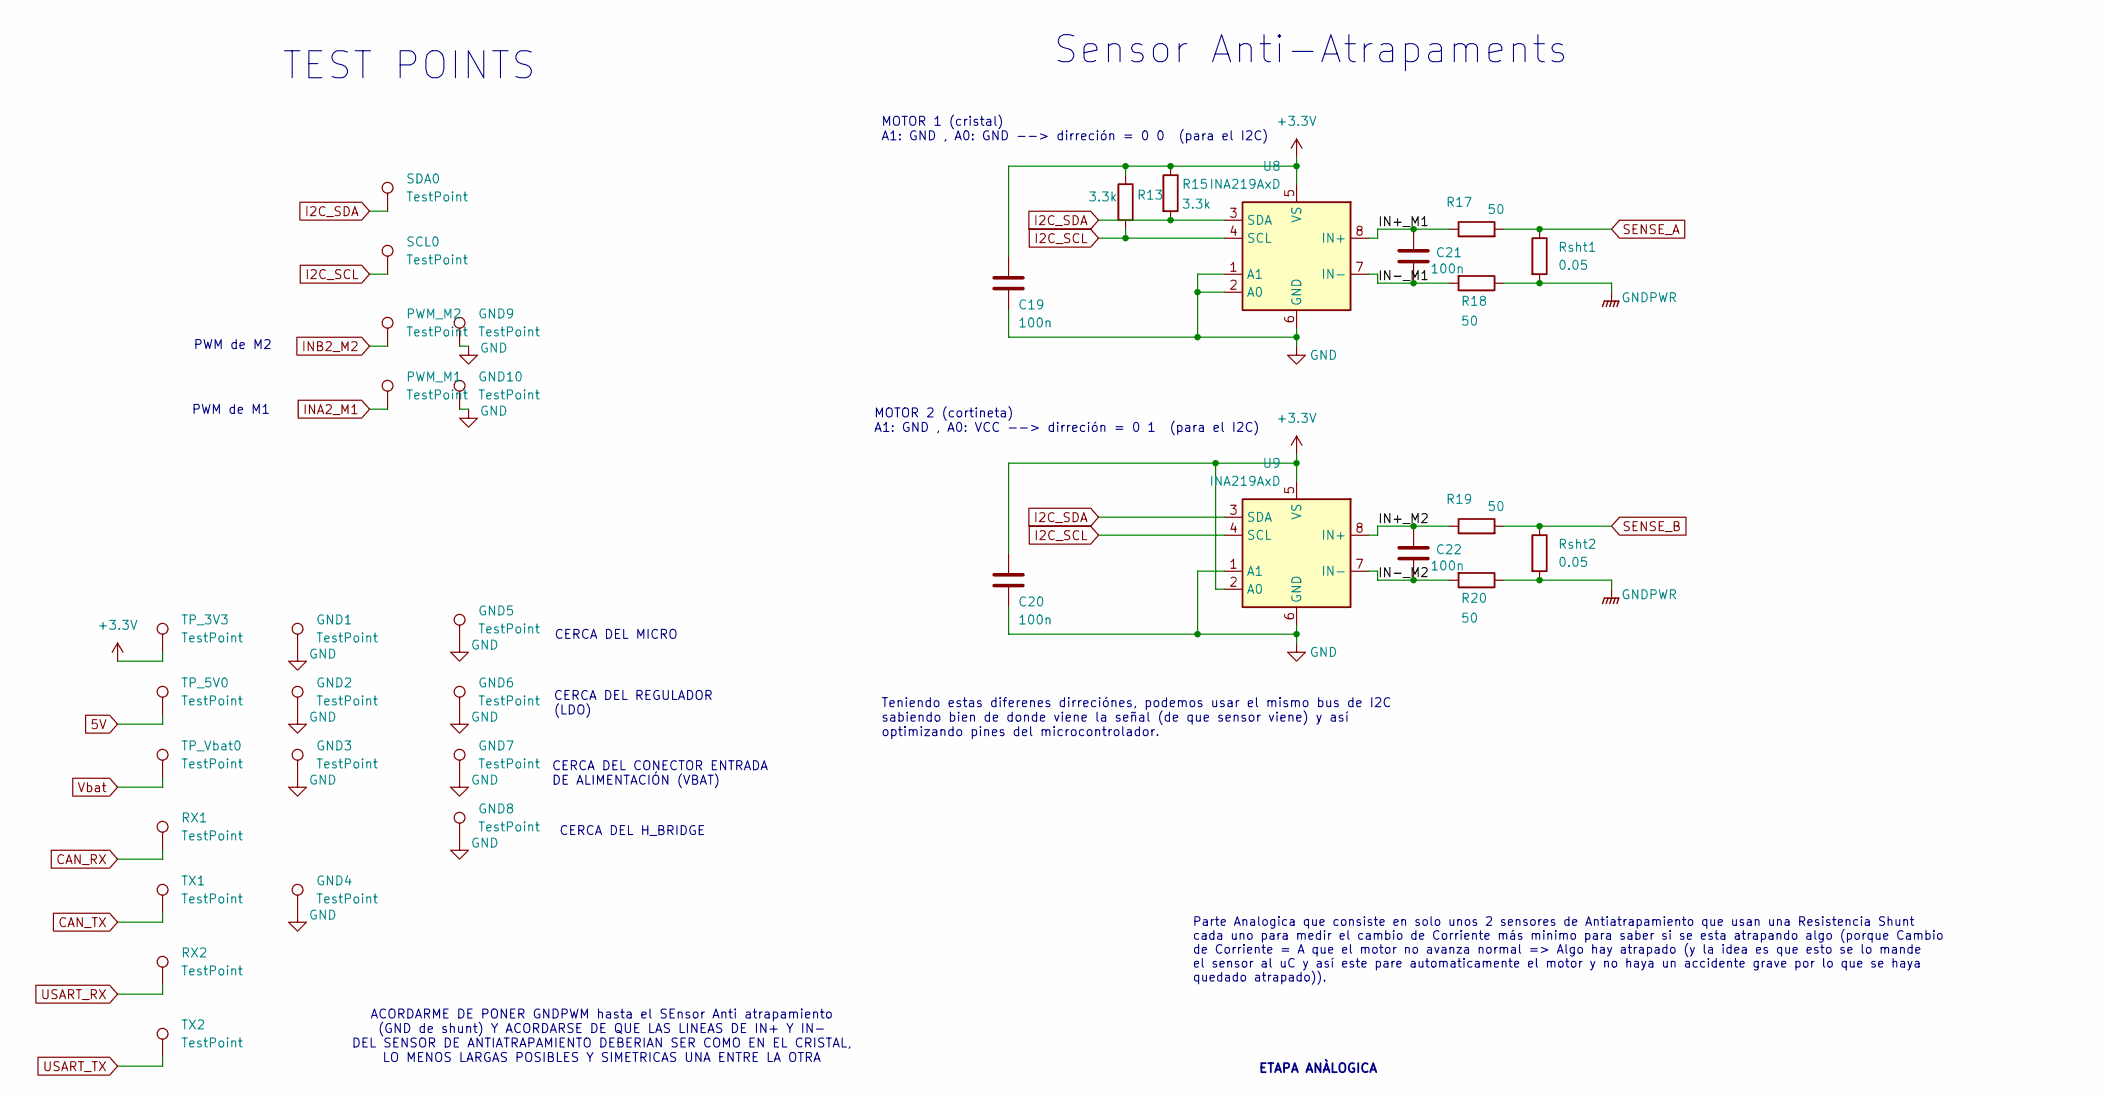
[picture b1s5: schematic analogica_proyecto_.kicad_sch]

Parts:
C19, C20, C21, C22: 100n; C_0805_2012Metric
GND1, GND2, GND3, GND4, GND5, GND6, GND7, GND8, GND9, GND10: TestPoint; TestPoint_Keystone_5000-5004_Miniature
PWM_M1, PWM_M2: TestPoint; TestPoint_Keystone_5000-5004_Miniature
R13, R15: 3.3k; R_0805_2012Metric
R17, R18, R19, R20: 50; R_0805_2012Metric
RX1, RX2: TestPoint; TestPoint_Keystone_5000-5004_Miniature
Rsht1, Rsht2: 0.05; R_0805_2012Metric
SCL0: TestPoint; TestPoint_Keystone_5000-5004_Miniature
SDA0: TestPoint; TestPoint_Keystone_5000-5004_Miniature
TP_3V3, TP_5V0: TestPoint; TestPoint_Keystone_5000-5004_Miniature
TP_Vbat0: TestPoint; TestPoint_Keystone_5000-5004_Miniature
TX1, TX2: TestPoint; TestPoint_Keystone_5000-5004_Miniature
U8, U9: INA219AxD; SOIC-8_3.9x4.9mm_P1.27mm

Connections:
5V: TP_5V0.1; also elsewhere on the board
+3.3V: C19.1, C20.1, R13.1, R15.1, TP_3V3.1, U8.5 (VS), U9.2 (A0), U9.5 (VS); also elsewhere on the board
/Analogica/IN+_M1: C21.1, R17.1, U8.8 (IN+)
/Analogica/IN+_M2: C22.1, R19.1, U9.8 (IN+)
/Analogica/IN-_M1: C21.2, R18.2, U8.7 (IN-)
/Analogica/IN-_M2: C22.2, R20.2, U9.7 (IN-)
CAN_RX: RX1.1; also elsewhere on the board
CAN_TX: TX1.1; also elsewhere on the board
GND: C19.2, C20.2, GND1.1, GND2.1, GND3.1, GND4.1, GND5.1, GND6.1, GND7.1, GND8.1, GND9.1, GND10.1, R18.1, R20.1, Rsht1.2, Rsht2.2, U8.1 (A1), U8.2 (A0), U8.6 (GND), U9.1 (A1), U9.6 (GND); also elsewhere on the board
I2C_SCL: R13.2, SCL0.1, U8.4 (SCL), U9.4 (SCL); also elsewhere on the board
I2C_SDA: R15.2, SDA0.1, U8.3 (SDA), U9.3 (SDA); also elsewhere on the board
INA2_M1: PWM_M1.1; also elsewhere on the board
INB2_M2: PWM_M2.1; also elsewhere on the board
SENSE_A: R17.2, Rsht1.1; also elsewhere on the board
SENSE_B: R19.2, Rsht2.1; also elsewhere on the board
USART_RX: RX2.1; also elsewhere on the board
USART_TX: TX2.1; also elsewhere on the board
Vbat: TP_Vbat0.1; also elsewhere on the board

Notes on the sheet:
Sensor Anti-Atrapaments
CERCA DEL CONECTOR ENTRADA DE ALIMENTACIÓN (VBAT)
PWM de M2
Teniendo estas diferenes dirreciónes, podemos usar el mismo bus de I2C sabiendo bien de donde viene la señal (de que sensor viene) y así optimizando pines del microcontrolador.
ETAPA ANÀLOGICA
MOTOR 1 (cristal) A1: GND , A0: GND --> dirreción = 0 0 (para el I2C)
PWM de M1
ACORDARME DE PONER GNDPWM hasta el SEnsor Anti atrapamiento (GND de shunt) Y ACORDARSE DE QUE LAS LINEAS DE IN+ Y IN- DEL SENSOR DE ANTIATRAPAMIENTO DEBERIAN SER COMO EN EL CRISTAL, LO MENOS LARGAS POSIBLES Y SIMETRICAS UNA ENTRE LA OTRA
CERCA DEL H_BRIDGE
Parte Analogica que consiste en solo unos 2 sensores de Antiatrapamiento que usan una Resistencia Shunt cada uno para medir el cambio de Corriente más minimo para saber si se esta atrapando algo (porque Cambio de Corriente = A que el motor no avanza normal => Algo hay atrapado (y la idea es que est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
MOTOR 2 (cortineta) A1: GND , A0: VCC --> dirreción = 0 1 (para el I2C)
CERCA DEL REGULADOR (LDO)
CERCA DEL MICRO
TEST POINTS
